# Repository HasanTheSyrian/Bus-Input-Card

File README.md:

8-bit bus input card for an 8-bit CPU bus. Power supply not ideal but (should) works.

Use KiCAD 7.

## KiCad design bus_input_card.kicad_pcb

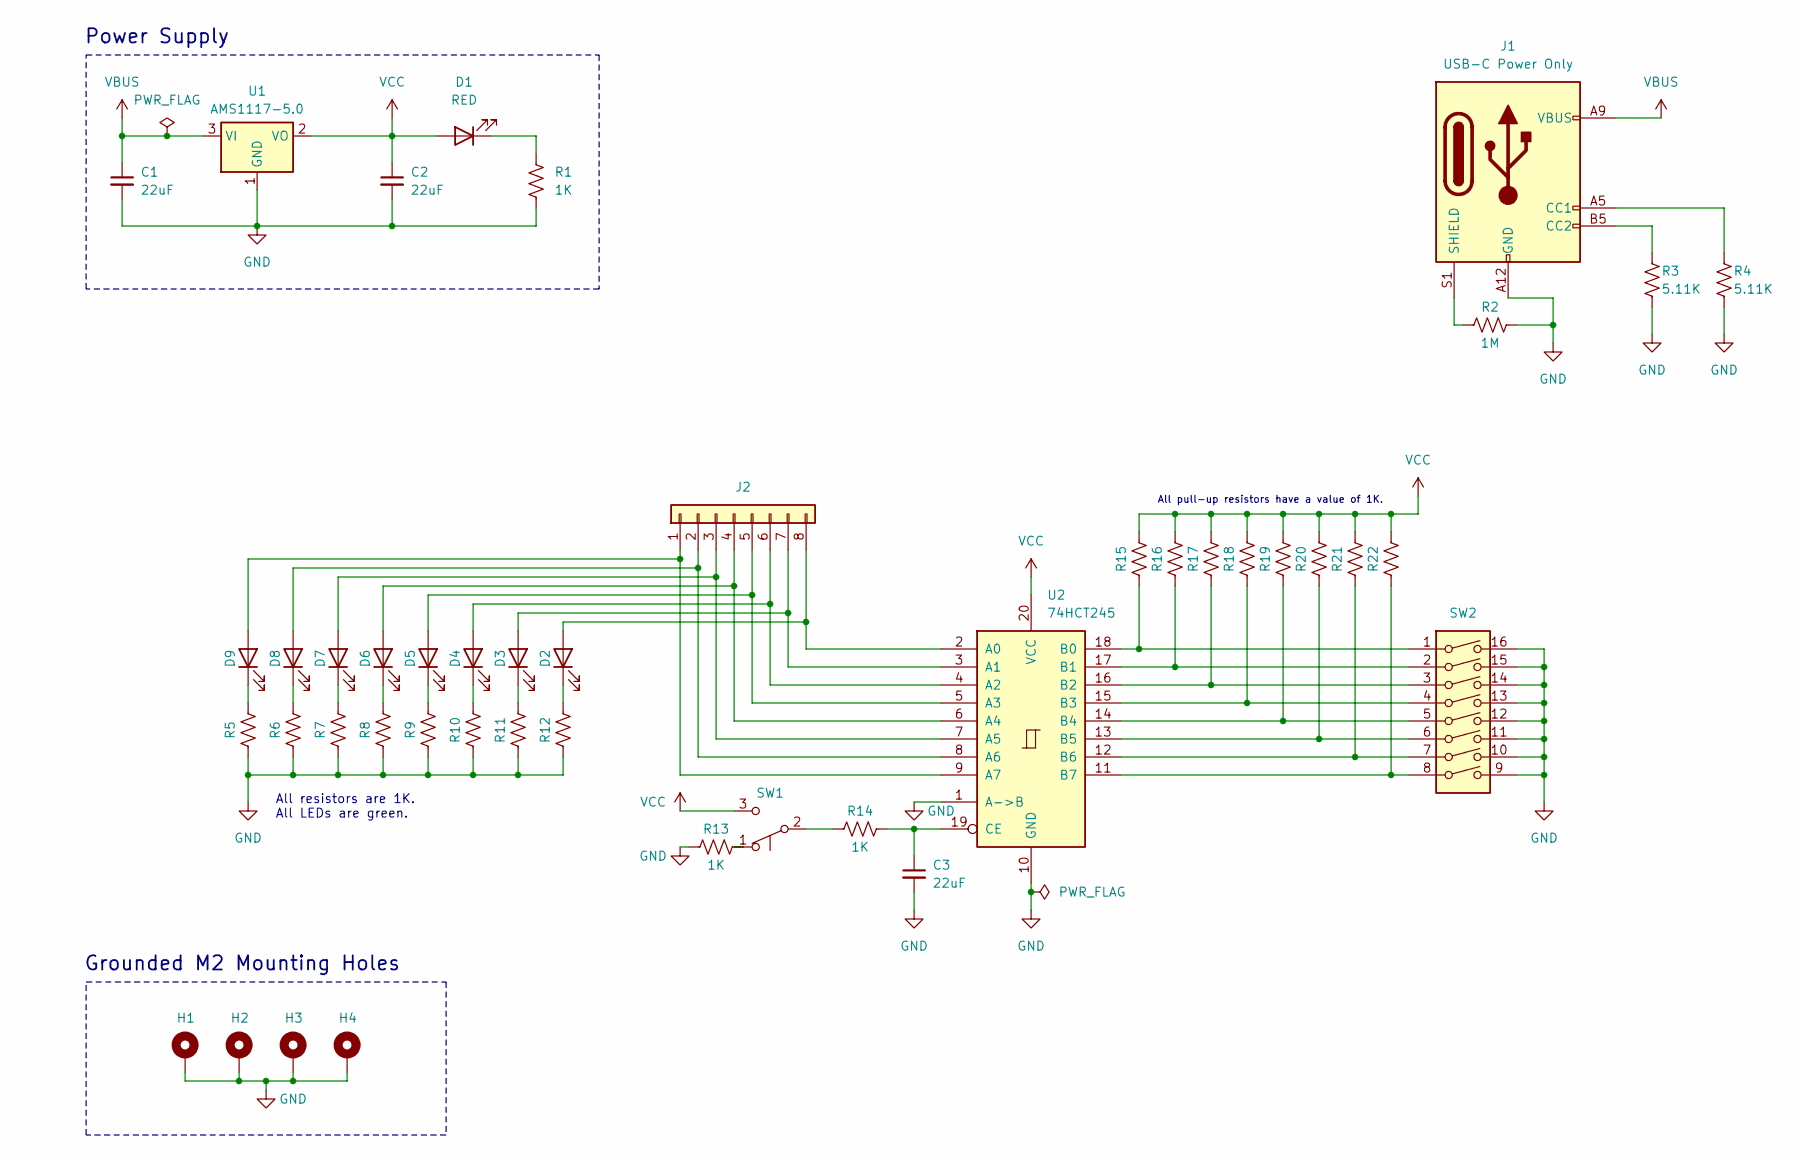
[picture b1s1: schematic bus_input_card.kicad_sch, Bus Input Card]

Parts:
C1, C2, C3: 22uF; C_0805_2012Metric
D1: RED; LED_1206_3216Metric
D2, D3, D4, D5, D6, D7, D8, D9: GREEN; LED_1206_3216Metric
H1, H2, H3, H4: MountingHole; MountingHole_2.2mm_M2_DIN965_Pad
J1: USB-C Power Only; USB_C_Receptacle_GCT_USB4135-GF-A_6P_TopMnt_Horizontal
J2: Pin Header; PinHeader_1x08_P2.54mm_Vertical
R1, R13, R14: 1K; R_0805_2012Metric
R2: 1M; R_0805_2012Metric
R3, R4: 5.11K; R_0805_2012Metric
R5, R6, R7, R8, R9, R10, R11, R12, R15, R16, R17, R18, R19, R20, R21, R22: 1k; R_0805_2012Metric
SW1: SW_Push_SPDT; SW_SPDT_CK-JS102011SAQN
SW2: SW_DIP_x08; SW_DIP_SPSTx08_Slide_Omron_A6H-8101_W6.15mm_P1.27mm
U1: AMS1117-5.0; SOT-223-3_TabPin2
U2: 74HCT245; SOP65P640X110-20N

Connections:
GND: C1.2, C2.2, C3.2, H1.1, H2.1, H3.1, H4.1, J1.A12 (GND), J1.B12 (GND), R1.1, R2.2, R3.2, R4.2, R5.1, R6.1, R7.1, R8.1, R9.1, R10.1, R11.1, R12.1, R13.1, SW2.9, SW2.10, SW2.11, SW2.12, SW2.13, SW2.14, SW2.15, SW2.16, U1.1 (GND), U2.1 (A->B), U2.10 (GND)
unnamed: D1.1 (K), R1.2
unnamed: D2.2 (A), J2.8, U2.2 (A0)
unnamed: D2.1 (K), R12.2
unnamed: D3.2 (A), J2.7, U2.3 (A1)
unnamed: D3.1 (K), R11.2
unnamed: D4.2 (A), J2.6, U2.4 (A2)
unnamed: D4.1 (K), R10.2
unnamed: D5.2 (A), J2.5, U2.5 (A3)
unnamed: D5.1 (K), R9.2
unnamed: D6.2 (A), J2.4, U2.6 (A4)
unnamed: D6.1 (K), R8.2
unnamed: D7.2 (A), J2.3, U2.7 (A5)
unnamed: D7.1 (K), R7.2
unnamed: D8.2 (A), J2.2, U2.8 (A6)
unnamed: D8.1 (K), R6.2
unnamed: D9.2 (A), J2.1, U2.9 (A7)
unnamed: D9.1 (K), R5.2
unnamed: J1.A5 (CC1), R4.1
unnamed: J1.B5 (CC2), R3.1
unnamed: J1.S1 (SHIELD), R2.1
unnamed: R13.2, SW1.1 (A)
unnamed: R14.1, SW1.2 (B)
unnamed: R15.1, SW2.1, U2.18 (B0)
unnamed: R16.1, SW2.2, U2.17 (B1)
unnamed: R17.1, SW2.3, U2.16 (B2)
unnamed: R18.1, SW2.4, U2.15 (B3)
unnamed: R19.1, SW2.5, U2.14 (B4)
unnamed: R20.1, SW2.6, U2.13 (B5)
unnamed: R21.1, SW2.7, U2.12 (B6)
unnamed: R22.1, SW2.8, U2.11 (B7)
unnamed: C3.1, R14.2, U2.19 (CE)
VBUS: C1.1, J1.A9 (VBUS), J1.B9 (VBUS), U1.3 (VI)
VCC: C2.1, D1.2 (A), R15.2, R16.2, R17.2, R18.2, R19.2, R20.2, R21.2, R22.2, SW1.3 (C), U1.2 (VO), U2.20 (VCC)

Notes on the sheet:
All resistors are 1K. All LEDs are green.
Power Supply
Grounded M2 Mounting Holes
All pull-up resistors have a value of 1K.

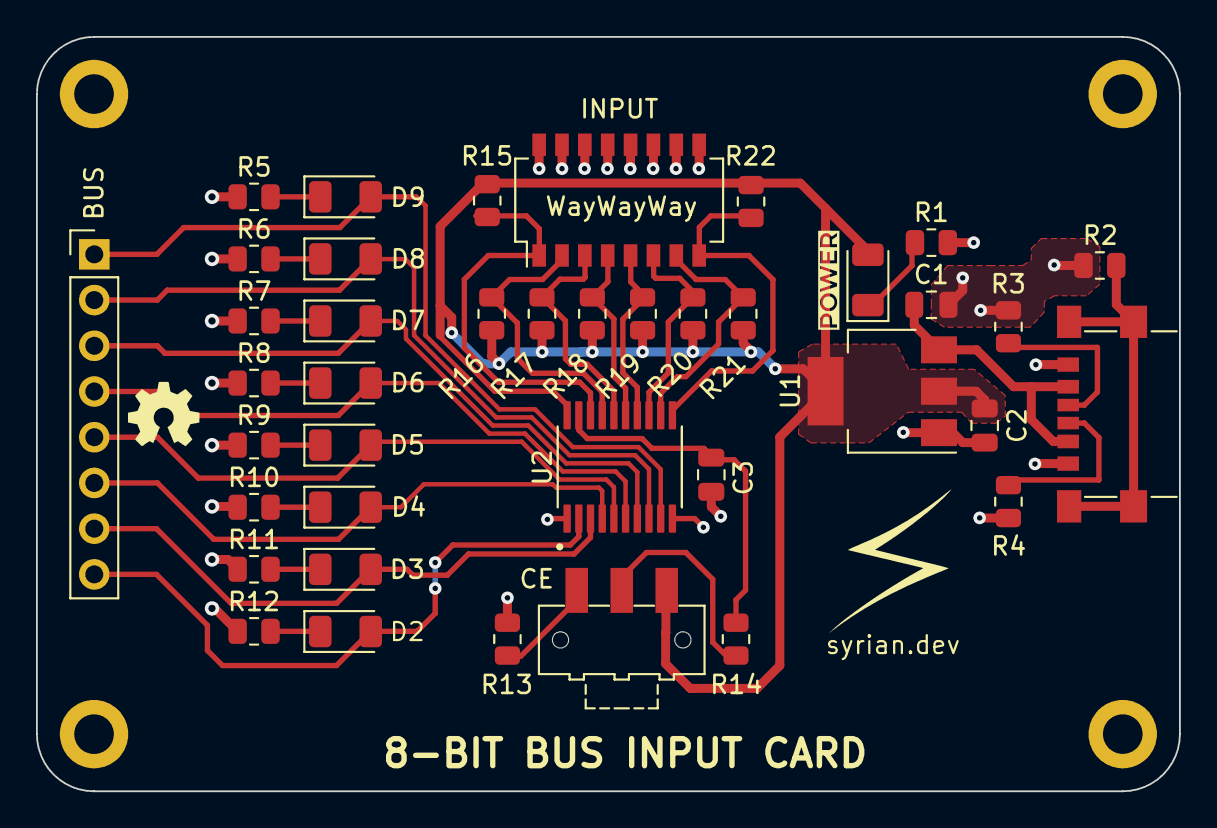
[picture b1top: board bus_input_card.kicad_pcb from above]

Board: 2 copper layers, 63.5 x 41.9 mm, 44 parts (0 on the bottom side), 34 nets.
